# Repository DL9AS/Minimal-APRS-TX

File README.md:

# Minimal APRS TX by DL9AS

**Note: This project is still in active development. There is no guarantee for full functionality at this time!**

The goal of this project is to provide one of the simplest APRS transmitters. It is especially designed for people who are starting high altitude ballooning. If you are interested in more advanced APRS radiosondes with camera, please have a look at this repository: https://github.com/DL9AS/jufo-project-radiosonde

The PCB requires only five components. The transmitter can be controlled with simple serial commands.

|  |  |
|:-------------------------------------------- |:------------------------------------------- |

## Table of contents

- [Minimal APRS TX by DL9AS](#minimal-aprs-tx-by-dl9as)
  - [Table of contents](#table-of-contents)
  - [Usage](#usage)
    - [`$STAT` *(Get status)*](#stat-get-status)
    - [`$CfgRadio` *(Configure APRS radio)*](#cfgradio-configure-aprs-radio)
    - [`$TxPosPkt` *(Transmit APRS position packet)*](#txpospkt-transmit-aprs-position-packet)
    - [`$TxStatPkt` *(Transmit APRS status packet)*](#txstatpkt-transmit-aprs-status-packet)
  - [PCB Assembly](#pcb-assembly)
  - [Programming](#programming)

## Usage

Only a few commands are required to use the Minimal APRS TX module. First the radio is configured with the command `$CfgRadio` and then APRS packets can be sent with the commands `$TXPosPkt` or `$TXStatPkt`.

For communication `9600 Baud` serial with 8 data bits, no parity, one stop bit is used. So it should communicate out of the box with any Arduino.

### `$STAT` *(Get status)*

```
Format:
$STAT;

Return:
[ACK] Minimal APRS TX - V1.0
```

### `$CfgRadio` *(Configure APRS radio)*

```
Format:
$CfgRadio <APRS_Freq>,<APRS_Freq_Err>,<TX_PWR>,<Afsk_Tone>,<Freq_Dev>,<Src_Call>,<Src_ID>,<Digi_Call>,<Digi_SSID>;

Example:
$CfgRadio 144800000,0,17,205,2700,DL9AS,11,WIDE1,1;
```

- `<APRS_Freq>` - APRS frequency in Hz (e.g. `144800000`)
- `<APRS_Freq_Err>` - APRS frequency error/offset in Hz (e.g. `0`)
- `<TX_PWR>` - Transmission power from 2dbm to 20dbm (e.g. `17`)
- `<Afsk_Tone>` - AFSK tone adjustment (e.g. `205`)
- `<Freq_Dev>` - FSK deviation in Hz (e.g. `2700`)
- `<Src_Call>` - APRS source callsign (e.g. `DL9AS`)
- `<Src_ID>` - APRS source SSID (e.g. `11`)
- `<Digi_Call>` - APRS digipeater path callsign (e.g. `WIDE1`)
- `<Digi_SSID>` - APRS digipeater path SSID (e.g. `1`)

### `$TxPosPkt` *(Transmit APRS position packet)*

```
Format:
$TxPosPkt <Lat>,<Long>,<Alt>,<Symbol>,<Symbol_Overlay>,<Comment>;

Example:
$TxPosPkt 525121,133273,42,O,/,"73 from DL9AS";

Resulting APRS packet:
DL9AS-11>AMON,WIDE1-1:!5230.72N/01319.63EO/A=000137/N0T26V31 73 from DL9AS
```

- `<Lat>` - GPS Latitude in deg * 10000 (e.g. `525121`)
- `<Long>` - GPS Longitude in deg * 10000 (e.g. `133273`)
- `<Alt>` - GPS Altitude in meters (e.g. `42`)
- `<Symbol>` - APRS symbol (e.g. `O` for balloon)
- `<Symbol_Overlay>` - APRS symbol overlay (e.g. `/` for balloon)
- `<Comment>` - APRS comment with 50 character max (e.g. `"73 from DL9AS"`)

Note: `(N<Pkt_count>T<Temperature>V<VCC*10>)` is automatically added to the final packet.

### `$TxStatPkt` *(Transmit APRS status packet)*

```
Format:
$TxStatPkt <Comment>;

Example:
$TxStatPkt "73 from DL9AS";

Resulting APRS packet:
DL9AS-1>AMON,WIDE1-1:>N0T0V31 73 from DL9AS
```

- `<Comment>` - APRS comment with 80 character max (e.g. `"73 from DL9AS"`)

Note: `(N<Pkt_count>T<Temperature>V<VCC*10>)` is automatically added to the final packet.

## PCB Assembly

<table>
  <tr>
    <td>In a first step, with the help of the <a href="Hardware/Gerber-Files/">gerber files</a>
, the custom PCBs are ordered from a PCB manufacturer. I would also recommend to order a stencil, that makes the soldering easier.</td>
    <td></td>
  </tr>
</table>

The needed components can now be ordered:

| Designator | Part                            | Quantity | Price (09.2023) |
| ---------- | ------------------------------- | -------- | --------------- |
| U1         | ATTiny1604                      | 1        | 0.81$           |
| U2         | SX1278IMLTRT                    | 1        | 2.65$           |
| X1         | 32MHz Crystal (SMD3225 package) | 1        | 0.15$           |
| C1         | 100nF (0402 package)            | 1        | 0.01$           |
| L1         | 200nH (0402 package)            | 1        | 0.01$           |

With the PCBs and the components, the transmitter can now be assembled. I would recommend reflow soldering with stencil. It is important that the correct orientation of the ICs is ensured. This [interactive BOM](https://htmlpreview.github.io/?https://github.com/DL9AS/Minimal-APRS-TX/blob/main/Hardware/InteractiveBOM.html) can help with placing the components.

## Programming

Before the Minimal APRS TX module can be used, the ATTiny1604 microcontroller has to be programmed. Here the firmware can be built from the source code or the ready binaries can be used. To keep these instructions as simple as possible, I will describe the second option.

1. First you want to install the `pymcuprog` utility. This requires Python and can be done using `pip install pymcuprog`.  See https://pypi.org/project/pymcuprog/ for more information.
2. Download the correct firmware binary from [here](Software/Binaries/).
3. Connect the USB to serial adapter and install serial drivers if necessary.
4. Run the following command to upload the firmware: 

```
pymcuprog write -d attiny1604 -t uart --erase --verify -u <PORT> -f <FIRMWARE>
```

- `<PORT>` - Serial Port (e.g. `COM5` or `ttyACM0`)
- `<FIRMWARE>` - Firmware file (e.g. `Minimal-APRS-TX_V1.0.hex`)

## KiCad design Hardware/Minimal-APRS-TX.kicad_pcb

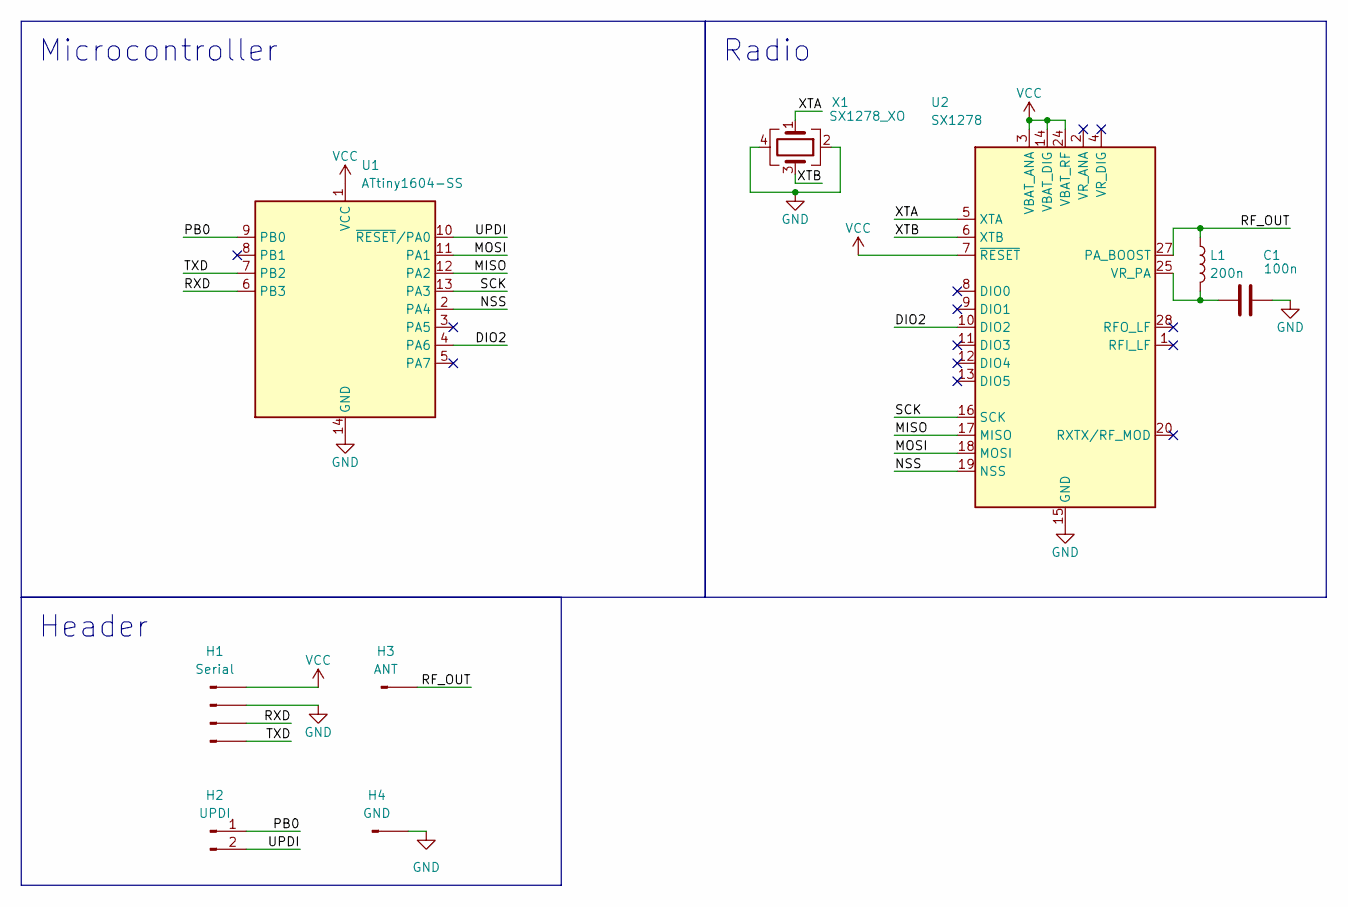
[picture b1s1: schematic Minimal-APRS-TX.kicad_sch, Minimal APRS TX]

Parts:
C1: 100n; C_0201_0603Metric
H1: Serial; My_PinHeader_4
H2: UPDI; My_PinHeader_2
H3: ANT; My_ANT_Pad
H4: GND; My_ANT_Pad
L1: 200n; L_0201_0603Metric
U1: ATtiny1604-SS; SOIC-14_3.9x8.7mm_P1.27mm
U2: SX1278; QFN-28-1EP_6x6mm_P0.65mm_EP4.8x4.8mm
X1: SX1278_XO; Crystal_SMD_3225-4Pin_3.2x2.5mm

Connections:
/DIO2: U1.4 (PA6), U2.10 (DIO2)
/MISO: U1.12 (PA2), U2.17 (MISO)
/MOSI: U1.11 (PA1), U2.18 (MOSI)
/NSS: U1.2 (PA4), U2.19 (NSS)
/PB0: H2.1, U1.9 (PB0)
/RF_OUT: H3.1, L1.1, U2.27 (PA_BOOST)
/RXD: H1.3, U1.6 (PB3)
/SCK: U1.13 (PA3), U2.16 (SCK)
/TXD: H1.4, U1.7 (PB2)
/UPDI: H2.2, U1.10 (~RESET/PA0)
/XTA: U2.5 (XTA), X1.1
/XTB: U2.6 (XTB), X1.3
GND: C1.2, H1.2, H4.1, U1.14 (GND), U2.15 (GND), U2.21 (GND), U2.22 (GND), U2.23 (GND), U2.26 (GND), U2.29 (GND), X1.2, X1.4
unnamed: C1.1, L1.2, U2.25 (VR_PA)
VCC: H1.1, U1.1 (VCC), U2.3 (VBAT_ANA), U2.7 (~RESET), U2.14 (VBAT_DIG), U2.24 (VBAT_RF)

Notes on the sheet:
Microcontroller
Radio
Header

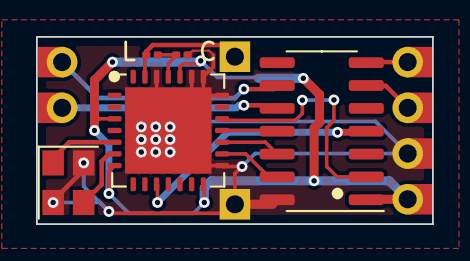
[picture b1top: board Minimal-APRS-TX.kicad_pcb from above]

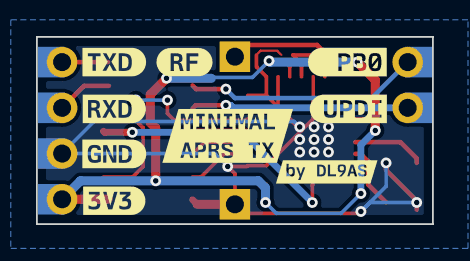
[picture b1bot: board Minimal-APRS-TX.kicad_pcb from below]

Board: 2 copper layers, 22.0 x 10.4 mm, 18 parts (9 on the bottom side), 15 nets.

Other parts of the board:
kibuzzard-64F1B3B3: G***; kibuzzard-64F1B3B3
kibuzzard-64F1B32F: G***; kibuzzard-64F1B32F
kibuzzard-64F1B34A: G***; kibuzzard-64F1B34A
kibuzzard-64F1B328: G***; kibuzzard-64F1B328
kibuzzard-64F1B334: G***; kibuzzard-64F1B334
kibuzzard-64F1B338: G***; kibuzzard-64F1B338
kibuzzard-64F1B350: G***; kibuzzard-64F1B350
kibuzzard-64F18FB8: G***; kibuzzard-64F18FB8
kibuzzard-64F18FF4: G***; kibuzzard-64F18FF4

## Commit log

2023-09-04 Init
2023-09-04 Fix README
2023-09-08 Add Software/Hardware files
2023-10-02 Update Documentation
